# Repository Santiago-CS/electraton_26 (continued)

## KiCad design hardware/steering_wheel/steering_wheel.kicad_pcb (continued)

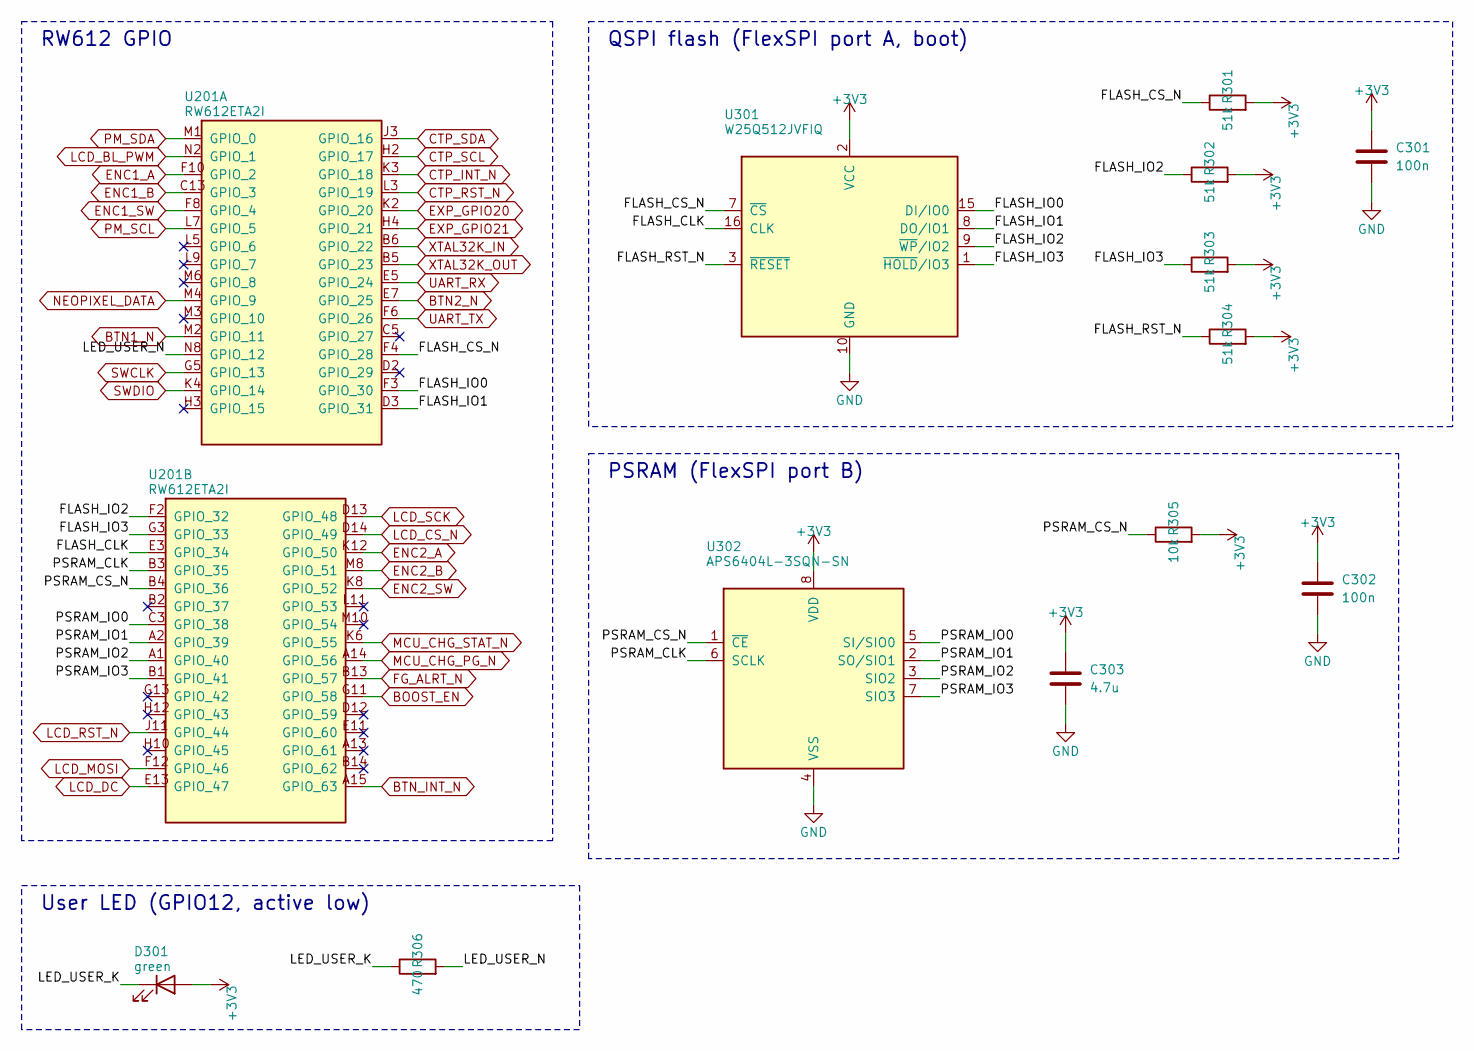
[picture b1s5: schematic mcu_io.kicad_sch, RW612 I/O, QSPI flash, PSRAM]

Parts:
C301, C302: 100n; C_0402_1005Metric
C303: 4.7u; C_0402_1005Metric
D301: green; LED_0603_1608Metric
R301, R302, R303, R304: 51k; R_0402_1005Metric
R305: 10k; R_0402_1005Metric
R306: 470; R_0402_1005Metric
U201: RW612ETA2I; NXP_TFBGA145_8x8mm_P0.5mm; MPN RW612ETA2I
U301: W25Q512JVFIQ; SOIC-16W_7.5x10.3mm_P1.27mm; MPN W25Q512JVFIQ; LCSC C2962011
U302: APS6404L-3SQN-SN; SOIC-8_3.9x4.9mm_P1.27mm; MPN APS6404L-3SQN-SN; LCSC C3028887

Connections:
+3V3: C301.1, C302.1, C303.1, D301.2 (A), R301.2, R302.2, R303.2, R304.2, R305.2, U301.2 (VCC), U302.8 (VDD); also elsewhere on the board
/mcu_io/FLASH_CLK: U201.E3 (GPIO_34), U301.16 (CLK)
/mcu_io/FLASH_CS_N: R301.1, U201.F4 (GPIO_28), U301.7 (~CS)
/mcu_io/FLASH_IO0: U201.F3 (GPIO_30), U301.15 (DI/IO0)
/mcu_io/FLASH_IO1: U201.D3 (GPIO_31), U301.8 (DO/IO1)
/mcu_io/FLASH_IO2: R302.1, U201.F2 (GPIO_32), U301.9 (~WP/IO2)
/mcu_io/FLASH_IO3: R303.1, U201.G3 (GPIO_33), U301.1 (~HOLD/IO3)
/mcu_io/FLASH_RST_N: R304.1, U301.3 (~RESET)
/mcu_io/LED_USER_K: D301.1 (K), R306.1
/mcu_io/LED_USER_N: R306.2, U201.N8 (GPIO_12)
/mcu_io/PSRAM_CLK: U201.B3 (GPIO_35), U302.6 (SCLK)
/mcu_io/PSRAM_CS_N: R305.1, U201.B4 (GPIO_36), U302.1 (~CE)
/mcu_io/PSRAM_IO0: U201.C3 (GPIO_38), U302.5 (SI/SIO0)
/mcu_io/PSRAM_IO1: U201.A2 (GPIO_39), U302.2 (SO/SIO1)
/mcu_io/PSRAM_IO2: U201.A1 (GPIO_40), U302.3 (SIO2)
/mcu_io/PSRAM_IO3: U201.B1 (GPIO_41), U302.7 (SIO3)
BOOST_EN: U201.G11 (GPIO_58); also elsewhere on the board
BTN1_N: U201.M2 (GPIO_11); also elsewhere on the board
BTN2_N: U201.E7 (GPIO_25); also elsewhere on the board
BTN_INT_N: U201.A15 (GPIO_63); also elsewhere on the board
CTP_INT_N: U201.K3 (GPIO_18); also elsewhere on the board
CTP_RST_N: U201.L3 (GPIO_19); also elsewhere on the board
CTP_SCL: U201.H2 (GPIO_17); also elsewhere on the board
CTP_SDA: U201.J3 (GPIO_16); also elsewhere on the board
ENC1_A: U201.F10 (GPIO_2); also elsewhere on the board
ENC1_B: U201.C13 (GPIO_3); also elsewhere on the board
ENC1_SW: U201.F8 (GPIO_4); also elsewhere on the board
ENC2_A: U201.K12 (GPIO_50); also elsewhere on the board
ENC2_B: U201.M8 (GPIO_51); also elsewhere on the board
ENC2_SW: U201.K8 (GPIO_52); also elsewhere on the board
EXP_GPIO20: U201.K2 (GPIO_20); also elsewhere on the board
EXP_GPIO21: U201.H4 (GPIO_21); also elsewhere on the board
FG_ALRT_N: U201.B13 (GPIO_57); also elsewhere on the board
GND: C301.2, C302.2, C303.2, U301.10 (GND), U302.4 (VSS); also elsewhere on the board
LCD_BL_PWM: U201.N2 (GPIO_1); also elsewhere on the board
LCD_CS_N: U201.D14 (GPIO_49); also elsewhere on the board
LCD_DC: U201.E13 (GPIO_47); also elsewhere on the board
LCD_MOSI: U201.F12 (GPIO_46); also elsewhere on the board
LCD_RST_N: U201.J11 (GPIO_44); also elsewhere on the board
LCD_SCK: U201.D13 (GPIO_48); also elsewhere on the board
MCU_CHG_PG_N: U201.A14 (GPIO_56); also elsewhere on the board
MCU_CHG_STAT_N: U201.K6 (GPIO_55); also elsewhere on the board
NEOPIXEL_DATA: U201.M4 (GPIO_9); also elsewhere on the board
PM_SCL: U201.L7 (GPIO_5); also elsewhere on the board
PM_SDA: U201.M1 (GPIO_0); also elsewhere on the board
SWCLK: U201.G5 (GPIO_13); also elsewhere on the board
SWDIO: U201.K4 (GPIO_14); also elsewhere on the board
UART_RX: U201.E5 (GPIO_24); also elsewhere on the board
UART_TX: U201.F6 (GPIO_26); also elsewhere on the board
XTAL32K_IN: U201.B6 (GPIO_22); also elsewhere on the board
XTAL32K_OUT: U201.B5 (GPIO_23); also elsewhere on the board

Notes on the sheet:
RW612 GPIO
QSPI flash (FlexSPI port A, boot)
PSRAM (FlexSPI port B)
User LED (GPIO12, active low)

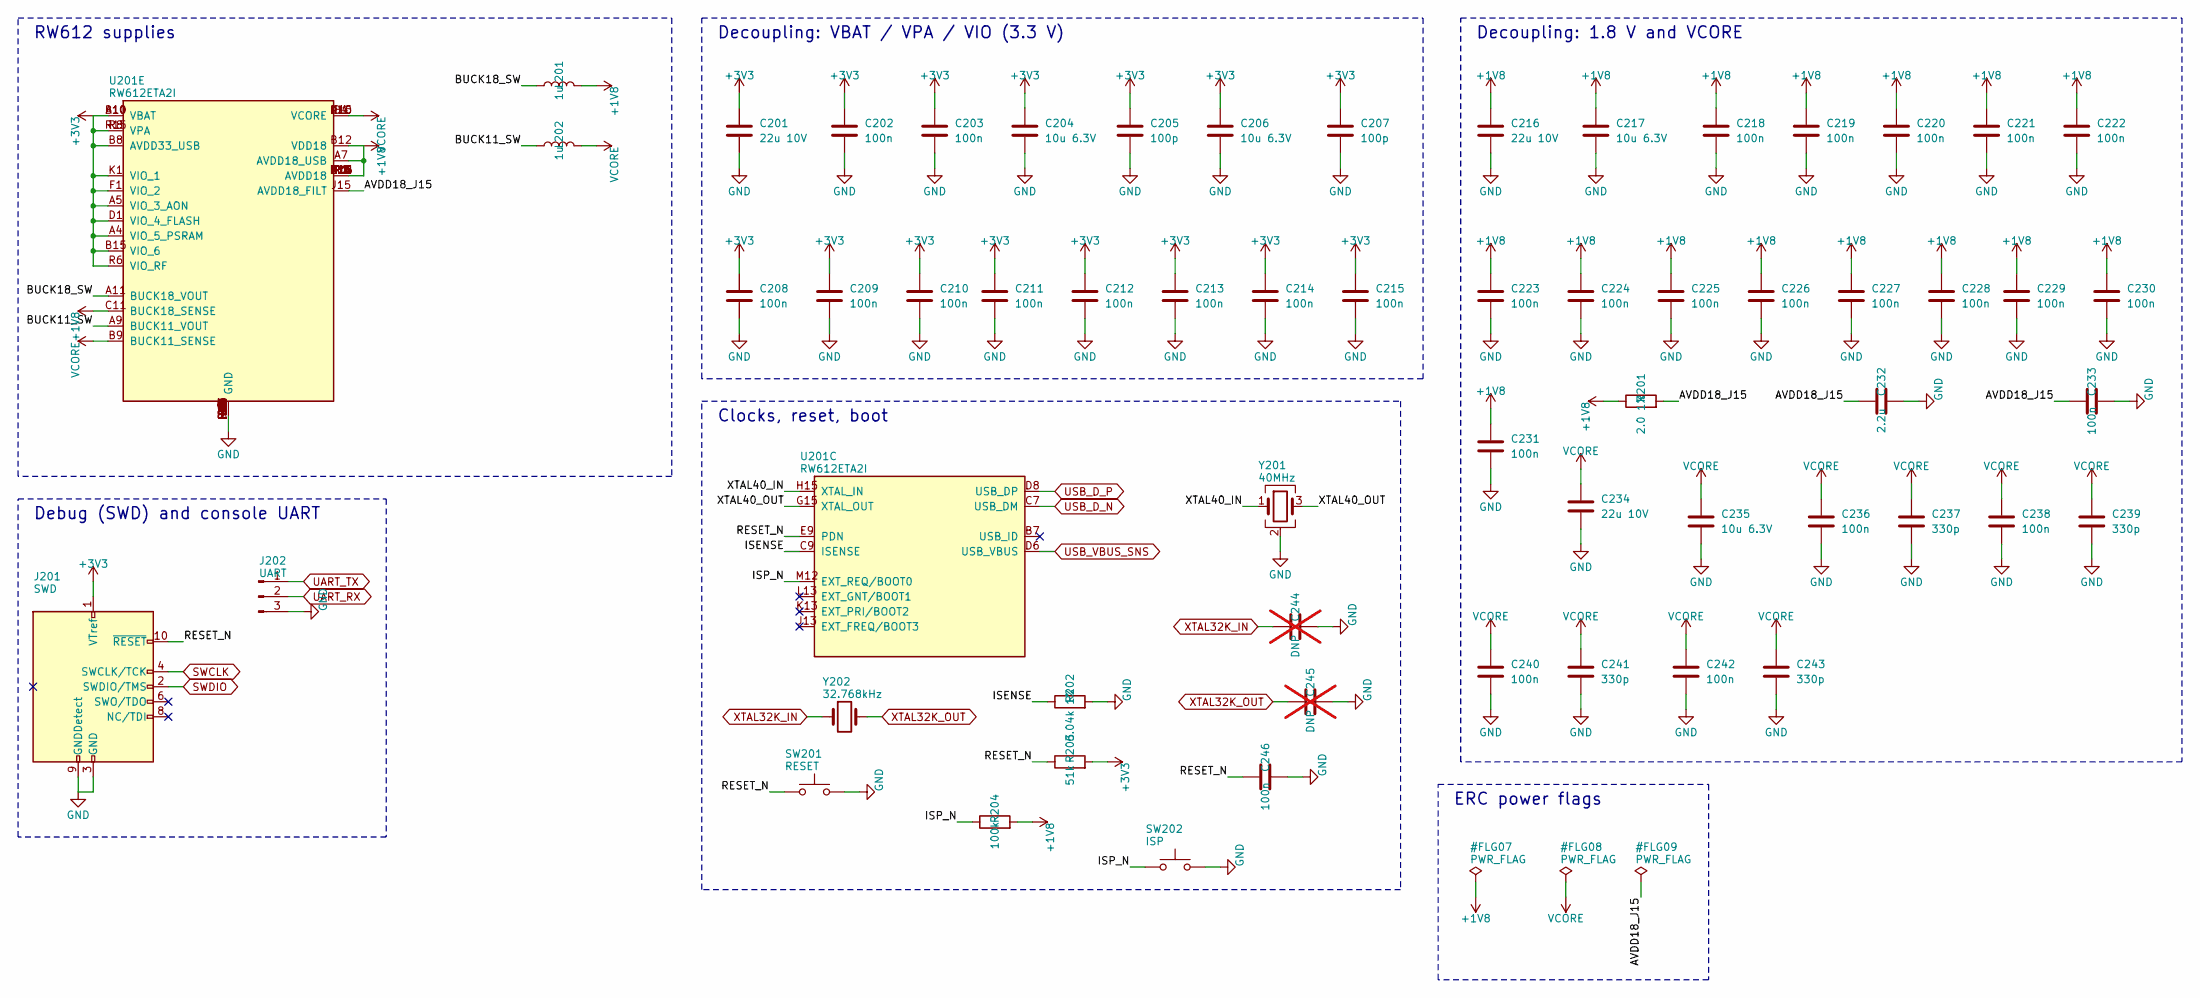
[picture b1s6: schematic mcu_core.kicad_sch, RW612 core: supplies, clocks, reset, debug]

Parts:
C201, C216, C234: 22u 10V; C_0603_1608Metric
C202, C203, C208, C209, C210, C211, C212, C213, C214, C215, C218, C219, C220, C221, C222, C223, C224, C225, C226, C227, C228, C229, C230, C231, C233, C236, C238, C240, C242: 100n; C_0201_0603Metric
C204, C206, C217, C235: 10u 6.3V; C_0402_1005Metric
C205, C207: 100p; C_0201_0603Metric
C232: 2.2u; C_0402_1005Metric
C237, C239, C241, C243: 330p; C_0201_0603Metric
C244, C245: DNP; C_0402_1005Metric; not fitted
C246: 100n; C_0402_1005Metric
J201: SWD; PinHeader_2x05_P1.27mm_Vertical_SMD; MPN Cortex 10-pin 1.27 mm
J202: UART; PinHeader_1x03_P2.54mm_Vertical
L201, L202: 1u; L_Wuerth_MAPI-2010; MPN 74438323010
R201: 2.0 1%; R_0402_1005Metric
R202: 6.04k 1%; R_0402_1005Metric
R203: 51k; R_0402_1005Metric
R204: 100k; R_0402_1005Metric
SW201: RESET; SW_SPST_TL3342; MPN TL3342F160QG
SW202: ISP; SW_SPST_TL3342; MPN TL3342F160QG
U201: RW612ETA2I; NXP_TFBGA145_8x8mm_P0.5mm; MPN RW612ETA2I
Y201: 40MHz; Crystal_SMD_2016-4Pin_2.0x1.6mm; MPN 8Q40070007
Y202: 32.768kHz; Crystal_SMD_3215-2Pin_3.2x1.5mm; MPN 830009678

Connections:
+1V8: C216.1, C217.1, C218.1, C219.1, C220.1, C221.1, C222.1, C223.1, C224.1, C225.1, C226.1, C227.1, C228.1, C229.1, C230.1, C231.1, L201.2, R201.1, R204.2, U201.A7 (AVDD18_USB), U201.B12 (VDD18), U201.C11 (BUCK18_SENSE), U201.F14 (AVDD18), U201.F15 (AVDD18), U201.K15 (AVDD18), U201.L15 (AVDD18), U201.M15 (AVDD18), U201.N15 (AVDD18), U201.P1 (AVDD18), U201.R1 (AVDD18), U201.R2 (AVDD18), U201.R10 (AVDD18), U201.R11 (AVDD18), U201.R12 (AVDD18)
+3V3: C201.1, C202.1, C203.1, C204.1, C205.1, C206.1, C207.1, C208.1, C209.1, C210.1, C211.1, C212.1, C213.1, C214.1, C215.1, J201.1 (VTref), R203.2, U201.A4 (VIO_5_PSRAM), U201.A5 (VIO_3_AON), U201.A10 (VBAT), U201.B8 (AVDD33_USB), U201.B10 (VBAT), U201.B15 (VIO_6), U201.D1 (VIO_4_FLASH), U201.F1 (VIO_2), U201.K1 (VIO_1), U201.R6 (VIO_RF), U201.R8 (VPA), U201.R15 (VPA); also elsewhere on the board
/mcu_core/AVDD18_J15: C232.1, C233.1, R201.2, U201.J15 (AVDD18_FILT)
/mcu_core/BUCK11_SW: L202.1, U201.A9 (BUCK11_VOUT)
/mcu_core/BUCK18_SW: L201.1, U201.A11 (BUCK18_VOUT)
/mcu_core/ISENSE: R202.1, U201.C9 (ISENSE)
/mcu_core/ISP_N: R204.1, SW202.1, U201.M12 (EXT_REQ/BOOT0)
/mcu_core/RESET_N: C246.1, J201.10 (~RESET), R203.1, SW201.1, U201.E9 (PDN)
/mcu_core/XTAL40_IN: U201.H15 (XTAL_IN), Y201.1
/mcu_core/XTAL40_OUT: U201.G15 (XTAL_OUT), Y201.3
GND: C201.2, C202.2, C203.2, C204.2, C205.2, C206.2, C207.2, C208.2, C209.2, C210.2, C211.2, C212.2, C213.2, C214.2, C215.2, C216.2, C217.2, C218.2, C219.2, C220.2, C221.2, C222.2, C223.2, C224.2, C225.2, C226.2, C227.2, C228.2, C229.2, C230.2, C231.2, C232.2, C233.2, C234.2, C235.2, C236.2, C237.2, C238.2, C239.2, C240.2, C241.2, C242.2, C243.2, C244.2, C245.2, C246.2, J201.3 (GND), J201.5 (GND), J201.9 (GNDDetect), J202.3, R202.2, SW201.2, SW202.2, U201.D10 (GND), U201.G7 (GND), U201.G8 (GND), U201.G9 (GND), U201.H6 (GND), U201.H7 (GND), U201.H9 (GND), U201.H13 (GND), U201.J5 (GND), U201.J7 (GND), U201.J8 (GND), U201.J9 (GND), U201.M13 (GND), U201.P2 (GND), U201.P4 (GND), U201.P8 (GND), U201.P9 (GND), U201.P10 (GND), U201.P11 (GND), U201.P12 (GND), U201.P13 (GND), U201.P14 (GND), U201.P15 (GND), U201.R3 (GND), U201.R5 (GND), U201.R7 (GND), U201.R13 (GND), Y201.2 (G), Y201.4 (G); also elsewhere on the board
SWCLK: J201.4 (SWCLK/TCK); also elsewhere on the board
SWDIO: J201.2 (SWDIO/TMS); also elsewhere on the board
UART_RX: J202.2; also elsewhere on the board
UART_TX: J202.1; also elsewhere on the board
USB_D_N: U201.C7 (USB_DM); also elsewhere on the board
USB_D_P: U201.D8 (USB_DP); also elsewhere on the board
USB_VBUS_SNS: U201.D6 (USB_VBUS); also elsewhere on the board
VCORE: C234.1, C235.1, C236.1, C237.1, C238.1, C239.1, C240.1, C241.1, C242.1, C243.1, L202.2, U201.B9 (BUCK11_SENSE), U201.D4 (VCORE), U201.D15 (VCORE), U201.H1 (VCORE), U201.K10 (VCORE)
XTAL32K_IN: C244.1, Y202.1; also elsewhere on the board
XTAL32K_OUT: C245.1, Y202.2; also elsewhere on the board

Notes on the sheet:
Clocks, reset, boot
Debug (SWD) and console UART
Decoupling: 1.8 V and VCORE
ERC power flags
RW612 supplies
Decoupling: VBAT / VPA / VIO (3.3 V)

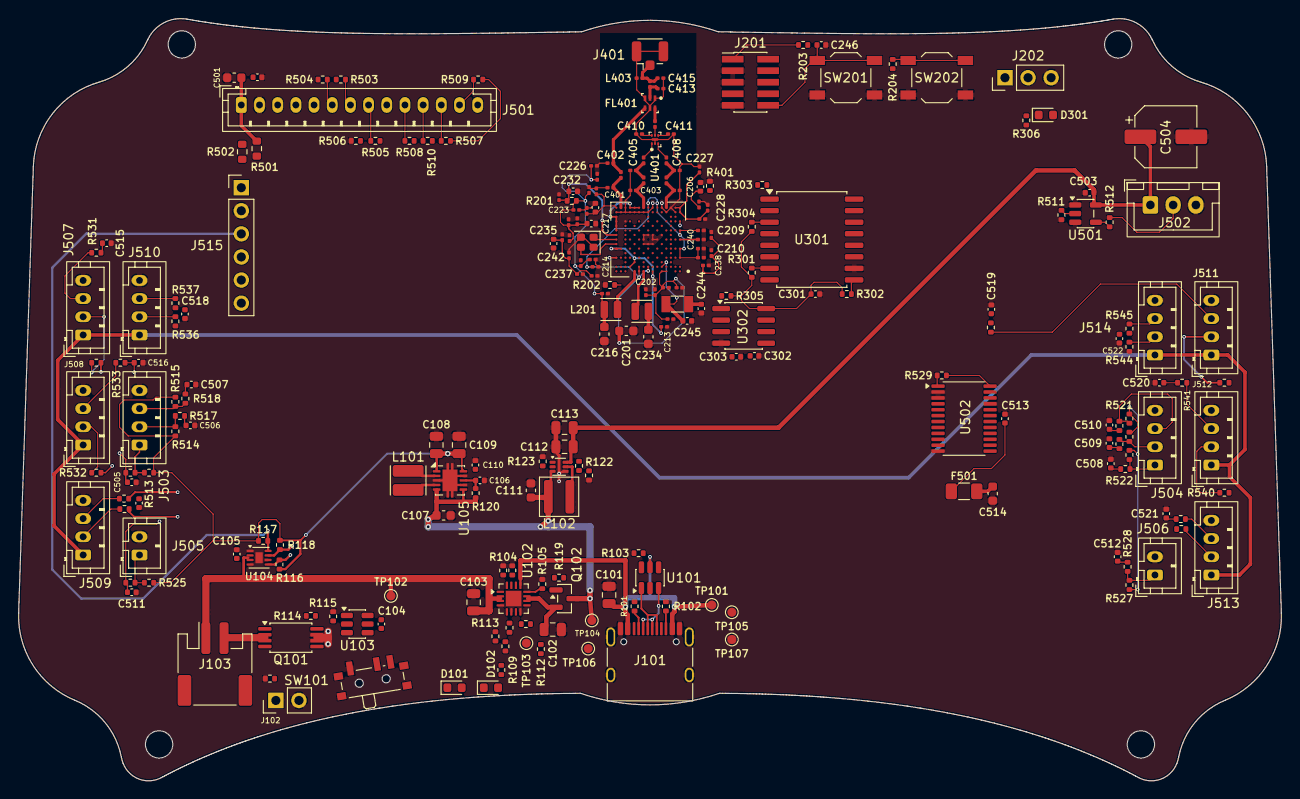
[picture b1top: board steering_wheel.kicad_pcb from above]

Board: 8 copper layers, 138.9 x 83.8 mm, 241 parts (0 on the bottom side), 152 nets.

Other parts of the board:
H1, H2, H3, H4: MountingHole; MountingHole_3mm

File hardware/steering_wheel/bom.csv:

Qty,References,Value,Footprint,MPN,Manufacturer,LCSC,DNP,Note
1,C101,10u 25V,C_0805_2012Metric,,,,,
2,C102 C103,10u 10V,C_0805_2012Metric,,,,,
14,C104 C105 C106 C110 C246 C301 C302 C502 C503 C507 C510 C511 C512 C513,100n,C_0402_1005Metric,,,,,
4,C107 C111 C501 C514,10u 10V,C_0603_1608Metric,,,,,
2,C108 C109,22u 6.3V,C_0805_2012Metric,,,,,
2,C112 C113,22u 10V,C_0805_2012Metric,,,,,
3,C201 C216 C234,22u 10V,C_0603_1608Metric,,,,,
29,C202 C203 C208 C209 C210 C211 C212 C213 C214 C215 C218 C219 C220 C221 C222 C223 C224 C225 C226 C227 C228 C229 C230 C231 C233 C236 C238 C240 C242,100n,C_0201_0603Metric,,,,,
4,C204 C206 C217 C235,10u 6.3V,C_0402_1005Metric,,,,,
4,C205 C207 C410 C411,100p,C_0201_0603Metric,,,,,
1,C232,2.2u,C_0402_1005Metric,,,,,
4,C237 C239 C241 C243,330p,C_0201_0603Metric,,,,,
1,C303,4.7u,C_0402_1005Metric,,,,,
2,C401 C402,0.3p,C_0201_0603Metric,,,,,
4,C404 C406 C409 C412,10p,C_0201_0603Metric,,,,,
2,C407 C408,1.6p,C_0201_0603Metric,,,,,
1,C414,5.6p,C_0201_0603Metric,,,,,antenna match (series)
1,C504,220u 6.3V,CP_Elec_6.3x5.4,,,,,bulk at strip connector
12,C505 C506 C508 C509 C515 C516 C517 C518 C519 C520 C521 C522,10n,C_0402_1005Metric,,,,,
1,D101,green,LED_0603_1608Metric,LED green 0603,,,,USB power good
1,D102,orange,LED_0603_1608Metric,LED orange 0603,,,,charging (off = full)
1,D301,green,LED_0603_1608Metric,,,,,
1,F501,0.2A,Fuse_1206_3216Metric,1206L020YR,Littelfuse,C207035,,0.2 A hold: a shorted button cable cannot pull down the MCU's 3.3 V
1,FL401,DPX165950DT-8085D1,TDK_DPX165950DT_1608_6T,DPX165950DT-8085D1,TDK,,,
1,J101,USB-C,USB_C_Receptacle_HRO_TYPE-C-31-M-12,TYPE-C-31-M-12,Korean Hroparts,C165948,,
1,J103,BATTERY,JST_PH_S2B-PH-SM4-TB_1x02-1MP_P2.00mm_Horizontal,S2B-PH-SM4-TB,JST,C295747,,"pin 1 = BAT+, pin 2 = BAT-; check pack polarity!"
1,J201,SWD,PinHeader_2x05_P1.27mm_Vertical_SMD,Cortex 10-pin 1.27 mm,,,,
1,J202,UART,PinHeader_1x03_P2.54mm_Vertical,,,,,FC3 console: 1=TX(out) 2=RX(in) 3=GND
1,J401,U.FL,U.FL_Hirose_U.FL-R-SMT-1_Vertical,U.FL-R-SMT-1(10),Hirose,C88373,,dual-band 2.4/5 GHz antenna
1,J501,LCD_MSP4031,JST_PH_B14B-PH-K_1x14_P2.00mm_Vertical,B14B-PH-K-S(LF)(SN),JST,C158024,,1 VCC 2 GND 3 CS 4 RST 5 DC 6 MOSI 7 SCK 8 LED 9 MISO 10 SCL 11 CTP_RST 12 SDA 13 INT 14 SD_CS (1:1 cable to the MSP4031 header)
1,J502,NEOPIXEL,JST_XH_B3B-XH-A_1x03_P2.50mm_Vertical,B3B-XH-A,JST,,,1=+5V 2=DIN 3=GND
1,J503,ENC1,JST_PH_B4B-PH-K_1x04_P2.00mm_Vertical,B4B-PH-K-S(LF)(SN),JST,C131334,,1=A 2=B 3=SW 4=GND (EC11 common C and switch return both to GND)
1,J504,ENC2,JST_PH_B4B-PH-K_1x04_P2.00mm_Vertical,B4B-PH-K-S(LF)(SN),JST,C131334,,1=A 2=B 3=SW 4=GND (EC11 common C and switch return both to GND)
1,J505,BTN1,JST_PH_B2B-PH-K_1x02_P2.00mm_Vertical,B2B-PH-K-S(LF)(SN),JST,C131337,,1=switch 2=GND
1,J506,BTN2,JST_PH_B2B-PH-K_1x02_P2.00mm_Vertical,B2B-PH-K-S(LF)(SN),JST,C131337,,1=switch 2=GND
1,J507,ABTN1,JST_PH_B4B-PH-K_1x04_P2.00mm_Vertical,B4B-PH-K-S(LF)(SN),JST,C131334,,1=VCC 2=in 3=out 4=GND
1,J508,ABTN2,JST_PH_B4B-PH-K_1x04_P2.00mm_Vertical,B4B-PH-K-S(LF)(SN),JST,C131334,,1=VCC 2=in 3=out 4=GND
1,J509,ABTN3,JST_PH_B4B-PH-K_1x04_P2.00mm_Vertical,B4B-PH-K-S(LF)(SN),JST,C131334,,1=VCC 2=in 3=out 4=GND
1,J510,ABTN4,JST_PH_B4B-PH-K_1x04_P2.00mm_Vertical,B4B-PH-K-S(LF)(SN),JST,C131334,,1=VCC 2=in 3=out 4=GND
1,J511,ABTN5,JST_PH_B4B-PH-K_1x04_P2.00mm_Vertical,B4B-PH-K-S(LF)(SN),JST,C131334,,1=VCC 2=in 3=out 4=GND
1,J512,ABTN6,JST_PH_B4B-PH-K_1x04_P2.00mm_Vertical,B4B-PH-K-S(LF)(SN),JST,C131334,,1=VCC 2=in 3=out 4=GND
1,J513,ABTN7,JST_PH_B4B-PH-K_1x04_P2.00mm_Vertical,B4B-PH-K-S(LF)(SN),JST,C131334,,1=VCC 2=in 3=out 4=GND
1,J514,ABTN8,JST_PH_B4B-PH-K_1x04_P2.00mm_Vertical,B4B-PH-K-S(LF)(SN),JST,C131334,,1=VCC 2=in 3=out 4=GND
1,J515,EXPANSION,PinHeader_1x06_P2.54mm_Vertical,,,,,1=3V3 2=GND 3=PM_SDA 4=PM_SCL 5=GPIO20 6=GPIO21
1,L101,2.2u,L_Wuerth_MAPI-3015,74438335022,Wurth,,,
1,L102,1u,L_Wuerth_MAPI-4020,74438357010,Wurth,,,
2,L201 L202,1u,L_Wuerth_MAPI-2010,74438323010,Wurth,,,
1,L401,1.6nH,L_0201_0603Metric,LQP03TN1N6B02D,Murata,,,
1,L402,3.3nH,L_0201_0603Metric,LQP03TN3N3B02D,Murata,,,
1,Q101,FS8205A,TSSOP-8_4.4x3mm_P0.65mm,FS8205A,Fortune Semiconductor,C16052,,
1,Q102,AO3401A,SOT-23,AO3401A,Alpha & Omega,C15127,,
2,R101 R102,5.1k,R_0402_1005Metric,,,,,
16,R103 R108 R109 R115 R518 R524 R526 R528 R531 R533 R535 R537 R539 R541 R543 R545,1k,R_0402_1005Metric,,,,,
1,R104,887 1%,R_0402_1005Metric,,,,,ICHG = 890/R = 1.0 A (590R -> 1.5 A)
1,R105,1.13k 1%,R_0402_1005Metric,,,,,IIN_MAX = 1610/R = 1.42 A
1,R106,68k,R_0402_1005Metric,,,,,safety timer: fast charge ~9 h (4000 mAh)
20,R107 R110 R111 R116 R305 R509 R510 R513 R514 R515 R516 R517 R519 R520 R521 R522 R523 R525 R527 R529,10k,R_0402_1005Metric,,,,,
7,R112 R113 R119 R123 R204 R506 R511,100k,R_0402_1005Metric,,,,,
11,R114 R120 R505 R530 R532 R534 R536 R538 R540 R542 R544,100,R_0402_1005Metric,,,,,
5,R117 R118 R401 R507 R508,4.7k,R_0402_1005Metric,,,,,
1,R121,732k 1%,R_0402_1005Metric,,,,,
1,R122,100k 1%,R_0402_1005Metric,,,,,
1,R201,2.0 1%,R_0402_1005Metric,,,,,AVDD18 J15 filter (FRDM R90)
1,R202,6.04k 1%,R_0402_1005Metric,,,,,RW612 bias reference
5,R203 R301 R302 R303 R304,51k,R_0402_1005Metric,,,,,
1,R306,470,R_0402_1005Metric,,,,,
1,R501,0,R_0603_1608Metric,,,,,LCD VCC = 5 V (default)
2,R503 R504,22,R_0402_1005Metric,,,,,
1,R512,330,R_0402_1005Metric,,,,,
1,SW101,PWR,SW_SPDT_PCM12,PCM12SMTR,C&K,C221841,,ON = pins 1-2 closed
1,SW201,RESET,SW_SPST_TL3342,TL3342F160QG,E-Switch,,,
1,SW202,ISP,SW_SPST_TL3342,TL3342F160QG,E-Switch,,,hold + reset = ISP boot (UART/USB)
1,TP101,VBUS,TestPoint_Pad_D1.0mm,,,,,
1,TP102,VBAT,TestPoint_Pad_D1.0mm,,,,,
1,TP103,VSYS,TestPoint_Pad_D1.0mm,,,,,
1,TP104,VSYS_SW,TestPoint_Pad_D1.0mm,,,,,
1,TP105,+3V3,TestPoint_Pad_D1.0mm,,,,,
1,TP106,+5V,TestPoint_Pad_D1.0mm,,,,,
1,TP107,GND,TestPoint_Pad_D1.0mm,,,,,
1,U101,USBLC6-2SC6,SOT-23-6,USBLC6-2SC6,STMicroelectronics,C7519,,
1,U102,BQ24074RGTR,VQFN-16-1EP_3x3mm_P0.5mm_EP1.68x1.68mm,BQ24074RGTR,Texas Instruments,C54313,,
1,U103,DW01A,SOT-23-6,DW01A,Fortune Semiconductor,C351410,,
1,U104,MAX17048G+T10,TDFN-8-1EP_2x2mm_P0.5mm_EP0.8x1.2mm,MAX17048G+T10,Analog Devices,C2682616,,
1,U105,TPS63001DRCR,VSON-10-1EP_3x3mm_P0.5mm_EP1.65x2.4mm,TPS63001DRCR,Texas Instruments,C28060,,
1,U106,TPS61023DRLR,SOT-563,TPS61023DRLR,Texas Instruments,C919459,,
1,U201,RW612ETA2I,NXP_TFBGA145_8x8mm_P0.5mm,RW612ETA2I,NXP,,,
1,U301,W25Q512JVFIQ,SOIC-16W_7.5x10.3mm_P1.27mm,W25Q512JVFIQ,Winbond,C2962011,,
1,U302,APS6404L-3SQN-SN,SOIC-8_3.9x4.9mm_P1.27mm,APS6404L-3SQN-SN,AP Memory,C3028887,,
1,U401,SKY13323-378LF,Skyworks_MLPD-6-1EP_1x1mm,SKY13323-378LF,Skyworks,C150867,,
1,U501,SN74AHCT1G125DBVR,SOT-23-5,SN74AHCT1G125DBVR,Texas Instruments,C7484,,
1,U502,TCA9555PWR,TSSOP-24_4.4x7.8mm_P0.65mm,TCA9555PWR,Texas Instruments,C465732,,
1,Y201,40MHz,Crystal_SMD_2016-4Pin_2.0x1.6mm,8Q40070007,TXC,,,"same crystal as FRDM-RW612, no load caps"
1,Y202,32.768kHz,Crystal_SMD_3215-2Pin_3.2x1.5mm,830009678,Wurth,,,on GPIO22/23 like FRDM-RW612
2,C244 C245,DNP,C_0402_1005Metric,,,,DNP,
4,C403 C405 C413 C415,DNP,C_0201_0603Metric,,,,DNP,
1,J102,BATT_NTC,PinHeader_1x02_P2.54mm_Vertical,,,,DNP,optional 10k NTC (103AT) from battery pack
1,L403,DNP,L_0201_0603Metric,,,,DNP,antenna match (shunt)
1,R502,0,R_0603_1608Metric,,,,DNP,alt: LCD VCC = 3.3 V

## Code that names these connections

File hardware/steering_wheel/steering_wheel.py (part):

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
with block("power", "Main power switch (charging still works when OFF)"):
    mk(SW, "SW_SPDT", "PWR", "Button_Switch_SMD:SW_SPDT_PCM12", mpn="PCM12SMTR", lcsc="C221841", mfr="C&K",
       note="ON = pins 1-2 closed", _2="PWR_SW_G", _1="GND", _3=None)
    mk("Transistor_FET", "Q_PMOS_GSD", "AO3401A", "Package_TO_SOT_SMD:SOT-23",
       mpn="AO3401A", lcsc="C15127", mfr="Alpha & Omega", G="PWR_SW_G", S="VSYS", D="VSYS_SW")
    R("100k", "VSYS", "PWR_SW_G")
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    0: "PM_SDA", 1: "LCD_BL_PWM", 2: "ENC1_A", 3: "ENC1_B", 4: "ENC1_SW", 5: "PM_SCL",
    6: None, 7: None, 8: None, 9: "NEOPIXEL_DATA", 10: None, 11: "BTN1_N",
    12: "LED_USER_N", 13: "SWCLK", 14: "SWDIO", 15: None, 16: "CTP_SDA", 17: "CTP_SCL",
    18: "CTP_INT_N", 19: "CTP_RST_N", 20: "EXP_GPIO20", 21: "EXP_GPIO21",
    22: "XTAL32K_IN", 23: "XTAL32K_OUT", 24: "UART_RX", 25: "BTN2_N", 26: "UART_TX",
    27: None, 28: "FLASH_CS_N", 29: None, 30: "FLASH_IO0", 31: "FLASH_IO1",
    32: "FLASH_IO2", 33: "FLASH_IO3", 34: "FLASH_CLK", 35: "PSRAM_CLK", 36: "PSRAM_CS_N",
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
with block("hmi", "Expansion header"):
    mk("Connector", "Conn_01x06_Pin", "EXPANSION", "Connector_PinHeader_2.54mm:PinHeader_1x06_P2.54mm_Vertical",
       note="1=3V3 2=GND 3=PM_SDA 4=PM_SCL 5=GPIO20 6=GPIO21",
       _1="+3V3", _2="GND", _3="PM_SDA", _4="PM_SCL", _5="EXP_GPIO20", _6="EXP_GPIO21")


# =====================================================================================
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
